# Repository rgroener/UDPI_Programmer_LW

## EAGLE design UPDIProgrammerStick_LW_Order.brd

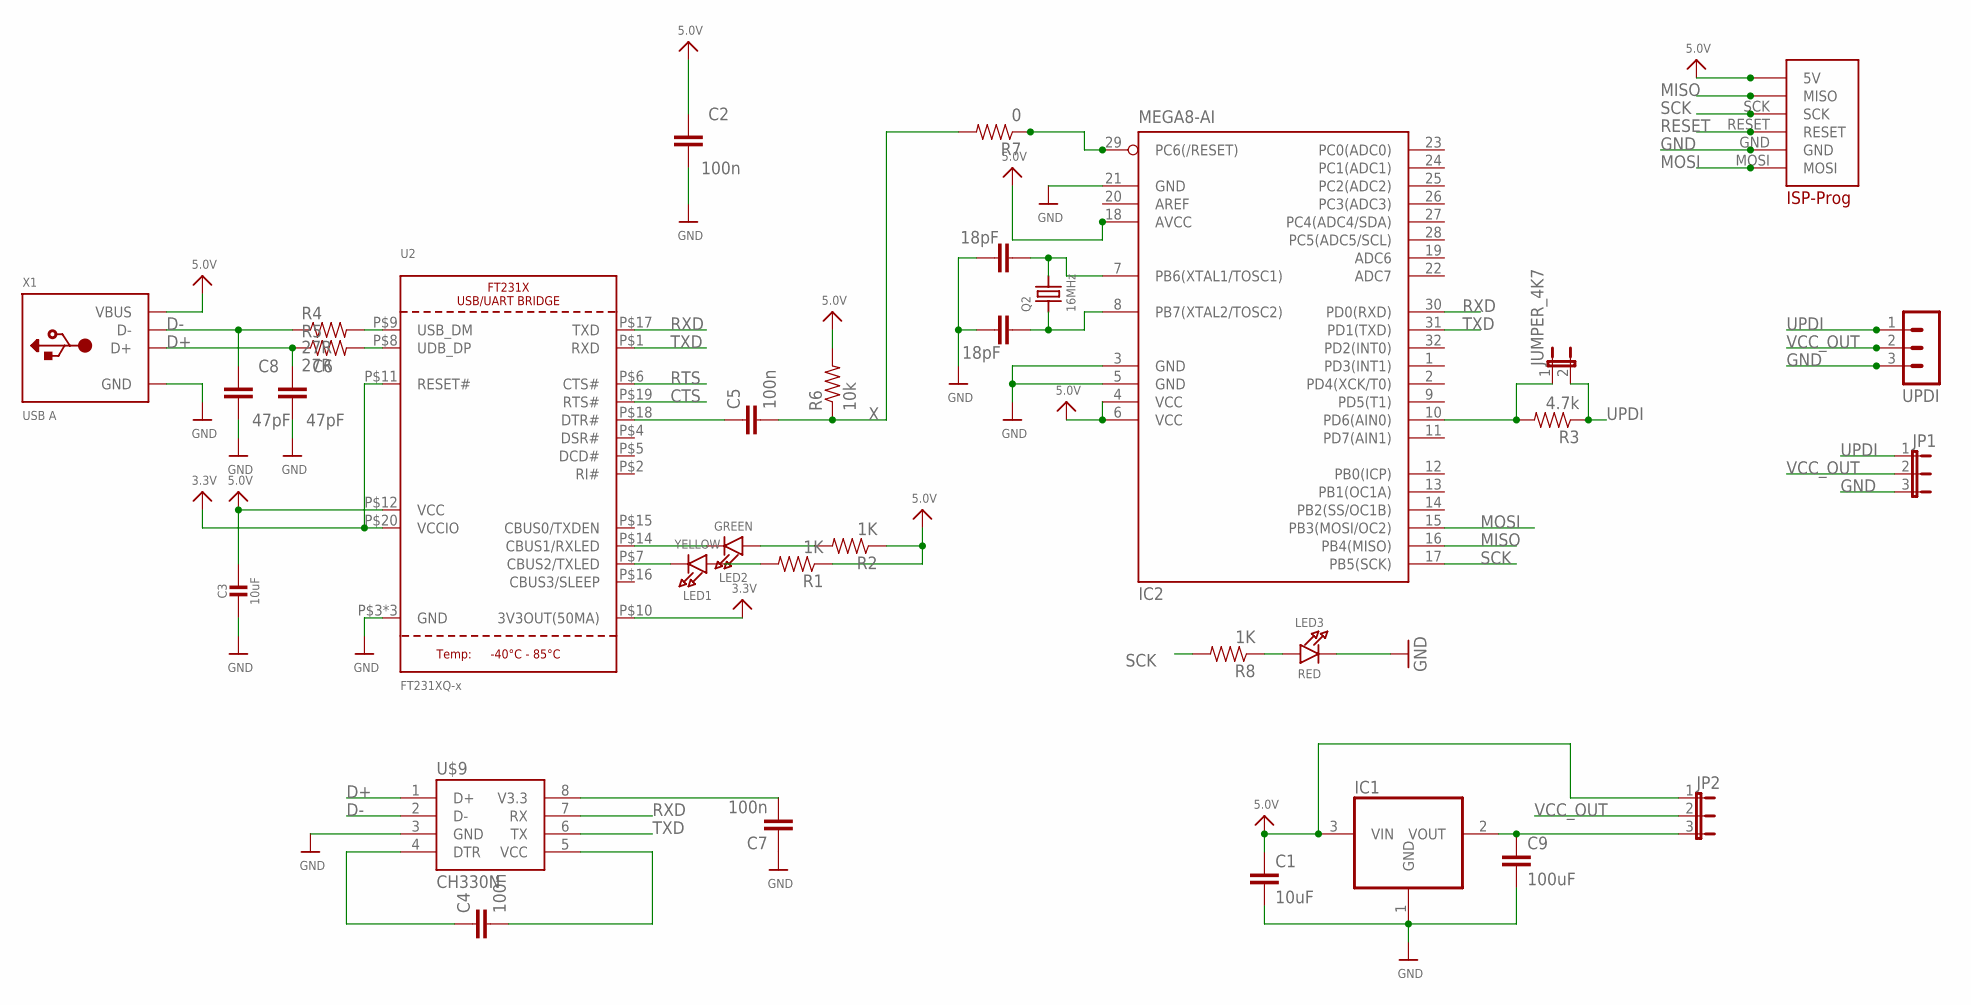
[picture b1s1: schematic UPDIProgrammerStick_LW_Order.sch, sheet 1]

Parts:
C1: 10uF; C1206
C2, C4, C5, C7: 100n; 0603-CAP
C3: 10uF; _1206
C6, C8: 47pF; 0603-CAP
C9: 100uF; C1206
C12, C13: 18pF; 0603-CAP
IC1: SOT223
IC2: MEGA8-AI; TQFP32-08
JP1, JP2: JP2E; JP2
JUMPER_4K7: JP1E; JP1
LED1: YELLOW; CHIPLED_0805_NOOUTLINE
LED2: GREEN; CHIPLED_0805_NOOUTLINE
LED3: RED; CHIPLED_0805_NOOUTLINE
Q2: 16MHz; CRYSTAL_3.2X2.5
R1, R2, R8: 1K; 0805
R3: 4.7k; 0805
R4, R5: 27R; 0805
R6: 10k; 0805
R7: 0; 0805
U2: FT231XQ-x; QFN20_4MM
U$6: ISP_PROG_STECKERISP_PROG_REIHE_DIP; ISP_PROG_REIHE_DIP
U$9: CH330N; SOIC8
UPDI: S3B-PH-K-S
X1: USB A; USB_A-THM

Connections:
3.3V: U2.P$10 (3V3OUT(50MA)), U2.P$11 (RESET#), U2.P$20 (VCCIO)
5.0V: C1.1, C2.1, C3.1, IC1.3 (VIN), IC2.4 (VCC), IC2.6 (VCC), IC2.18 (AVCC), JP2.1, R1.1, R2.1, R6.2, U2.P$12 (VCC), U$6.5V, X1.VBUS
CTS: U2.P$19 (RTS#)
D+: C6.1, R5.1, U$9.1 (D+), X1.D+
D-: C8.1, R4.1, U$9.2 (D-), X1.D-
GND: C1.2, C2.2, C3.2, C6.2, C7.1, C8.2, C9.2, C12.2, C13.2, IC1.1 (GND), IC2.3 (GND), IC2.5 (GND), IC2.21 (GND), JP1.3, LED3.C, U2.P$3 (GND), U2.P$13 (GND), U2.P$21 (GND), U$6.GND, U$9.3 (GND), UPDI.3, X1.GND
MISO: IC2.16 (PB4(MISO)), U$6.MISO
MOSI: IC2.15 (PB3(MOSI/OC2)), U$6.MOSI
unnamed: LED2.A, R2.2
unnamed: C12.1, IC2.7 (PB6(XTAL1/TOSC1)), Q2.2
unnamed: IC2.10 (PD6(AIN0)), JUMPER_4K7.1, R3.2
unnamed: LED1.A, R1.2
unnamed: LED1.C, U2.P$7 (CBUS2/TXLED)
unnamed: LED2.C, U2.P$14 (CBUS1/RXLED)
unnamed: C7.2, U$9.8 (V3.3)
unnamed: C13.1, IC2.8 (PB7(XTAL2/TOSC2)), Q2.1
unnamed: C9.1, IC1.2 (VOUT), JP2.3
unnamed: C4.2, U$9.5 (VCC)
unnamed: R5.2, U2.P$8 (UDB_DP)
unnamed: LED3.A, R8.1
unnamed: C4.1, U$9.4 (DTR)
unnamed: R4.2, U2.P$9 (USB_DM)
unnamed: C5.1, U2.P$18 (DTR#)
RESET: IC2.29 (PC6(/RESET)), R7.1, U$6.RESET
RTS: U2.P$6 (CTS#)
RXD: IC2.30 (PD0(RXD)), U2.P$17 (TXD), U$9.7 (RX)
SCK: IC2.17 (PB5(SCK)), R8.2, U$6.SCK
TXD: IC2.31 (PD1(TXD)), U2.P$1 (RXD), U$9.6 (TX)
UPDI: JP1.1, JUMPER_4K7.2, R3.1, UPDI.1
VCC_OUT: JP1.2, JP2.2, UPDI.2
X: C5.2, R6.1, R7.2

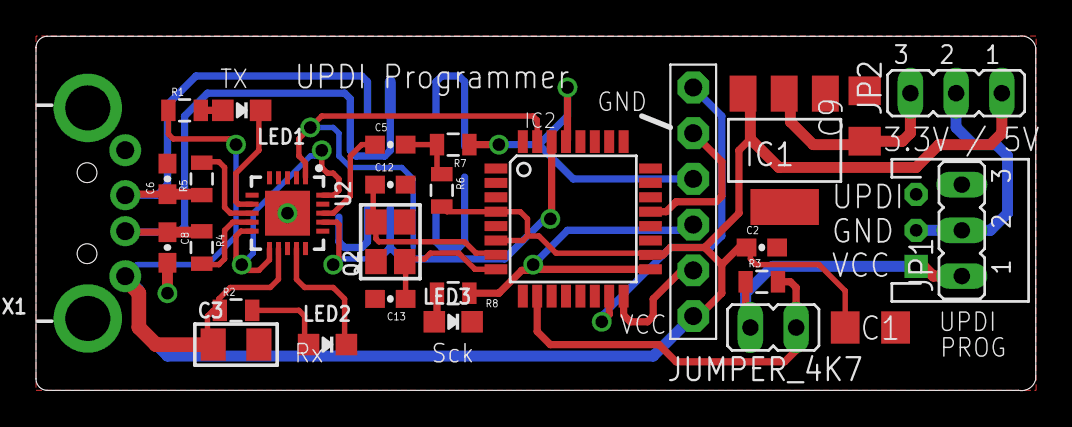
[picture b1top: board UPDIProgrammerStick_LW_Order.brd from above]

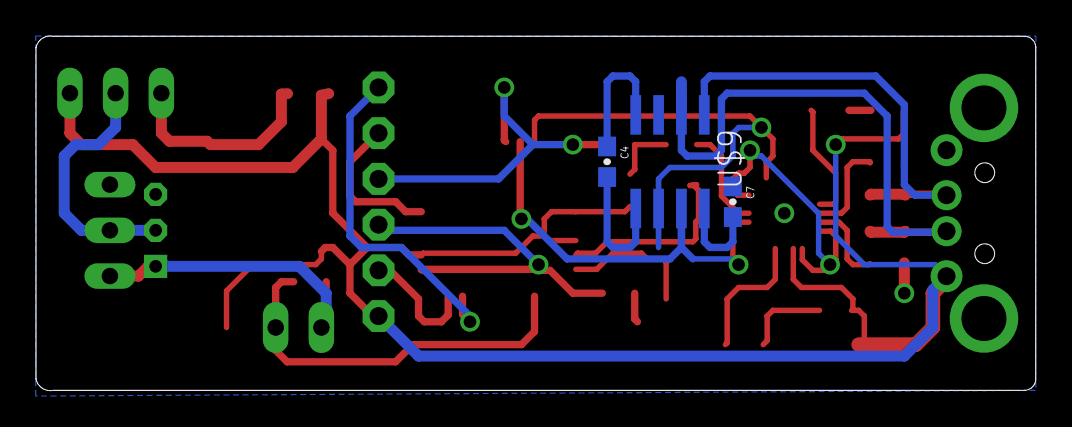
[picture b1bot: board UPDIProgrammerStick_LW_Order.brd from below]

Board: 2 copper layers, 55.5 x 19.7 mm, 33 parts (3 on the bottom side), 29 nets.

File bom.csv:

Qty,Value,Device,Package,Parts,Description,Distrelec,Farnell,Alternative,Preis,PE,Remark
2,,JP2E,JP2,"JP1, JP2",JUMPER,124-50-887,,,0.15,25,
1,3.3V,REG1117,SOT223,IC1,800mA and 1A (LDO) Positive Regulator,300-41-532,,,0.67,3Stk,
1, ,S3B-PH-K-S,S3B-PH-K-S,UPDI,"JST PH  2.00mm pitch, 3 pins",143-01-945,,Aliexpress,0.2,10,
1,0,0.3OHM-1/8W-1%(0805),805,R7,RES-11622,301-58-958,,,0.07,25,
4,100n,CAP0603-CAP,603,"C2, C4, C5, C7",Capacitor,300-86-429,,,0.009,100,
1,100uF,C-EUC1206,1206,C9,"CAPACITOR, European symbol",167-70-804,,,0.9,5,
1,10k,0.3OHM-1/8W-1%(0805),805,R6,RES-11622,,,Lager,,,
2,10uF,C-EUC1206,1206,C1,"CAPACITOR, European symbol",167-73-261,,,0.33,10,
1,16MHz,CRYSTALTHIN,CRYSTAL_3.2X2.5,Q2,Crystals,,2509429,,1.33,,
2,18pF,CAP0603-CAP,603,"C12, C13",Capacitor,300-86-534,,,0.009,100,
3,1K,0.3OHM-1/8W-1%(0805),805,"R1, R2, R8",RES-11622,,,Lager,,,
2,27R,0.3OHM-1/8W-1%(0805),805,"R4, R5",RES-11622,,,Lager,,,
1,4.7k,0.3OHM-1/8W-1%(0805),805,R3,RES-11622,,,Lager,,,
2,47pF,CAP0603-CAP,603,"C6, C8",Capacitor,300-86-566,,,0.03,100,
1,CH330N,CH330N,SOIC8,U$9,,,,Aliexpress,,,
1,FT231XQ-x ,FT231X,QFN20_4MM,U2,FT231X USB UART IC,,2081330,,2,,
1,GREEN,LED0805_NOOUTLINE,805,LED2,LED,300-08-873,,Lager,,,
1,ISP,ISP CONNECTOR,ISP_PROG_REIHE_DIP,U$6,,143-65-375,,,1.05,3,
1,MEGA8-AI,MEGA8-AI,TQFP32-08,IC2,MICROCONTROLLER,173-67-212,9171371,,2.95 / 2.19,1,
1,RED,LED0805_NOOUTLINE,805,LED3,LED,175-18-709,,Lager,,,
1,USB A,USB_TYPEA_CLIENTTHM,USB_A-THM,X1,USB - Type A Connectors,300-65-154,2067044,,1.88 / 1.16,3,
1,YELLOW,LED0805_NOOUTLINE,805,LED1,LED,,,Lager,,,

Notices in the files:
parts and their libraries:
SparkFun-Capacitors: Licensing: CC v3.0 Share-Alike You are welcome to use this library for commercial purposes.
microbuilder: This work is placed in the public domain, and may be freely used for commercial and non-commercial work with the following conditions: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
